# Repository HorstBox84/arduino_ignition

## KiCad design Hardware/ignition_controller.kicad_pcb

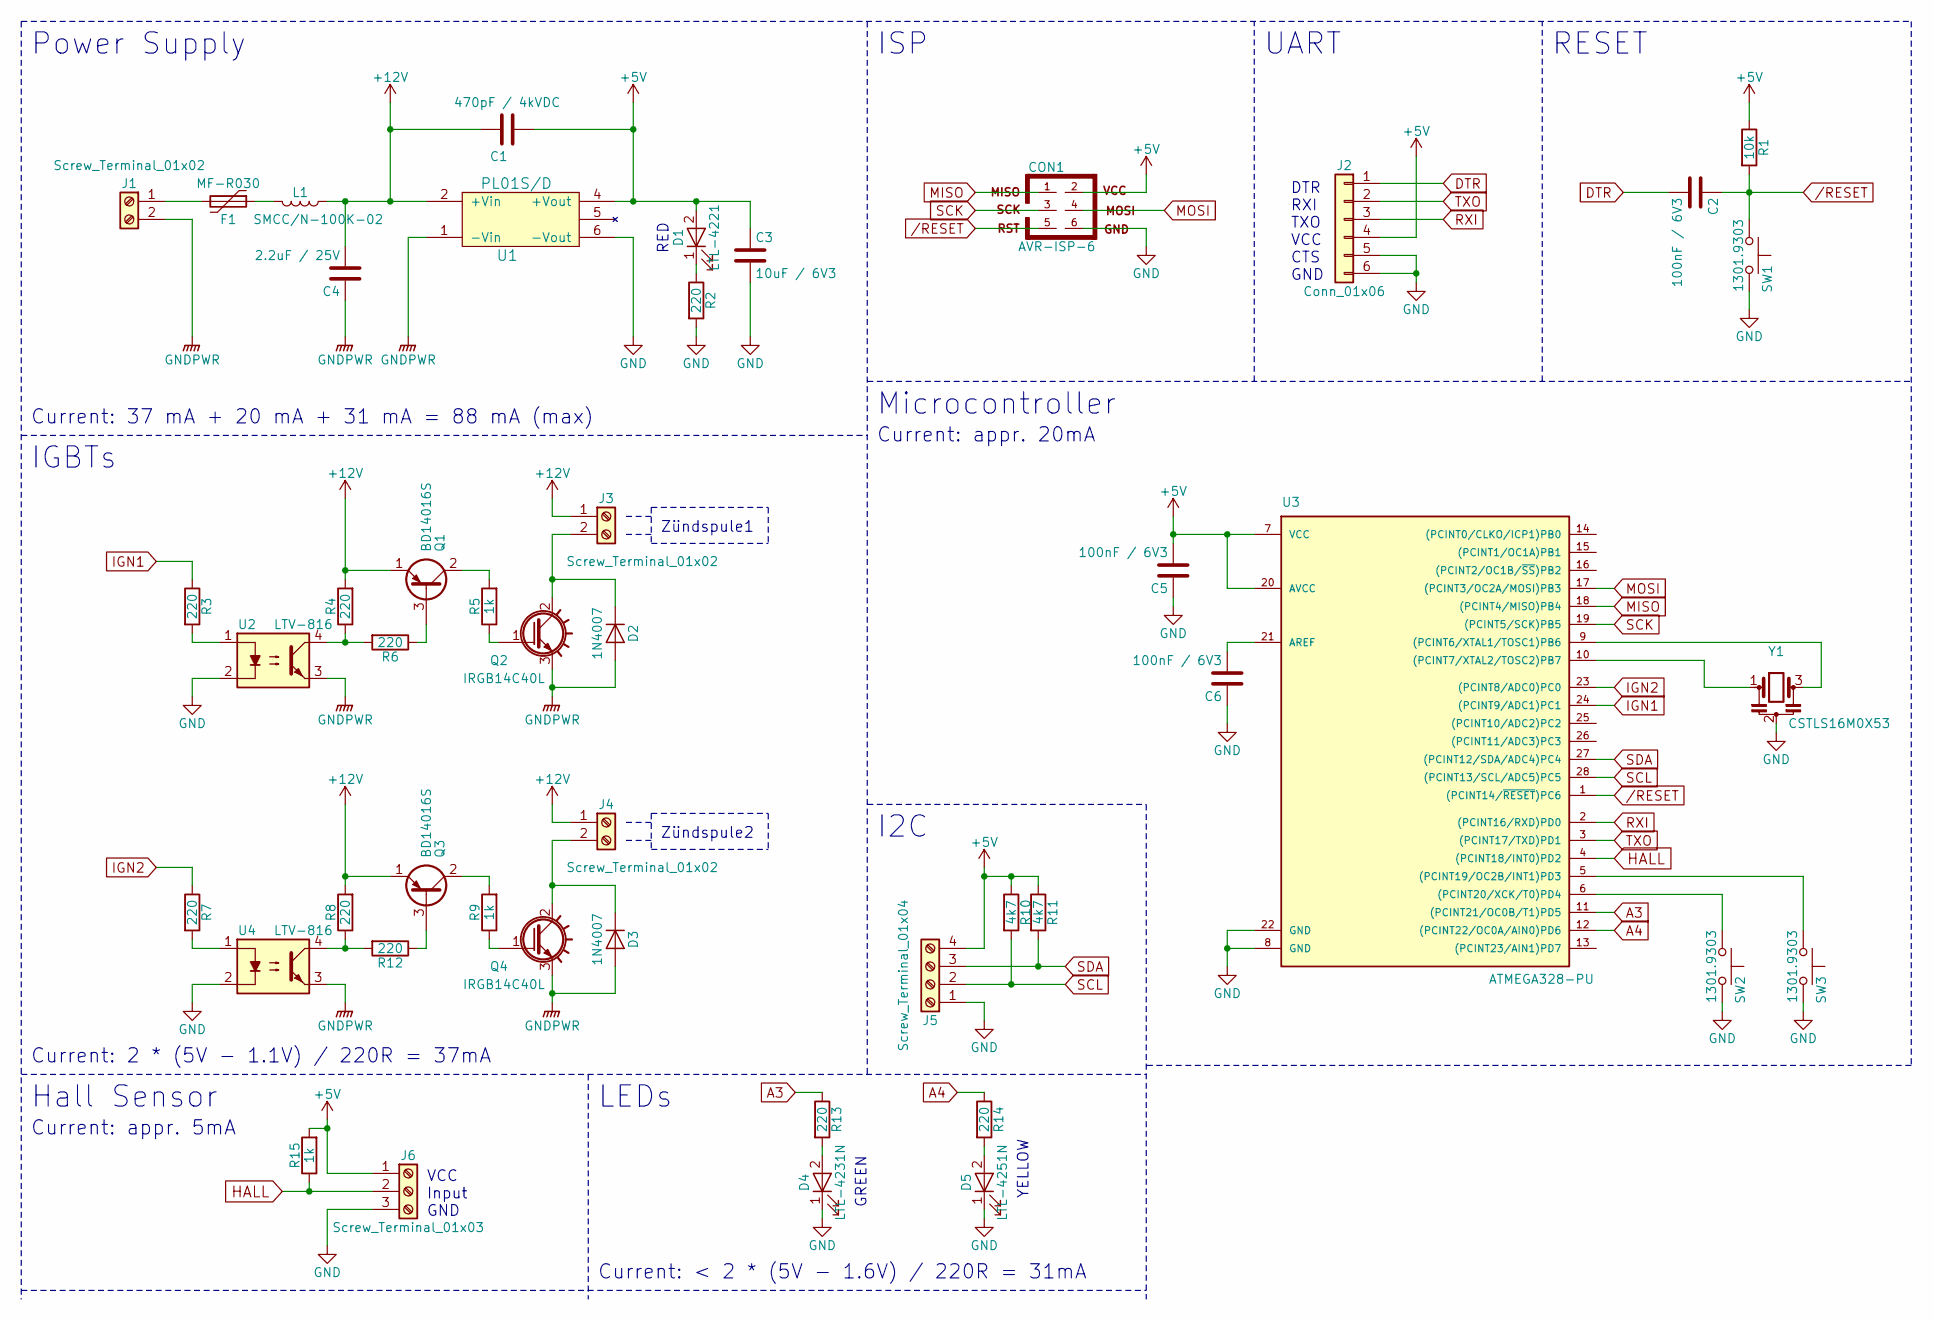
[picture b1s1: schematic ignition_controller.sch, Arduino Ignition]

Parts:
C1: 470pF / 4kVDC; C_Disc_D6_P5
C2, C5, C6: 100nF / 6V3; C_Disc_D3_P2.5
C3: 10uF / 6V3; C_Disc_D6_P5
C4: 2.2uF / 25V; C_Disc_D3_P2.5
CON1: AVR-ISP-6; Pin_Header_Straight_2x03_Pitch2.54mm
D1: LTL-4221; LED-3MM
D2, D3: 1N4007; Diode_DO-41_SOD81_Vertical_KathodeUp
D4: LTL-4231N; LED-3MM
D5: LTL-4251N; LED-3MM
F1: MF-R030; C_Disc_D7.5_P5
J1, J3, J4: Screw_Terminal_01x02; TerminalBlock_Pheonix_PT-3.5mm_2pol
J2: Conn_01x06; Pin_Header_Straight_1x06_Pitch2.54mm
J5: Screw_Terminal_01x04; TerminalBlock_Pheonix_PT-3.5mm_4pol
J6: Screw_Terminal_01x03; TerminalBlock_Pheonix_PT-3.5mm_3pol
L1: SMCC/N-100K-02; Resistor_Vertical_RM5mm
Q1, Q3: BD14016S; TO-126_Vertical
Q2, Q4: IRGB14C40L; TO-220_Neutral123_Vertical
R1: 10k; Resistor_Vertical_RM5mm
R2, R3, R4, R6, R7, R8, R12, R13, R14: 220; Resistor_Vertical_RM5mm
R5, R9, R15: 1k; Resistor_Vertical_RM5mm
R10, R11: 4k7; Resistor_Vertical_RM5mm
SW1, SW2, SW3: 1301.9303; SW_PUSH_6mm_h7.3mm
U1: PL01S/D; DCDC-Conv_TRACO_TMR_1-xxxx_Dual
U2, U4: LTV-816; DIP-4_W7.62mm
U3: ATMEGA328-PU; DIP-28_W7.62mm_LongPads
Y1: CSTLS16M0X53; Resonator-3pin_w6.0mm_h3.0mm

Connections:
+5V: C1.1, C3.1, C5.2, CON1.2, D1.2 (A), J2.4, J5.4, J6.1, R1.1, R10.1, R11.1, R15.2, U1.4 (+Vout), U3.7 (VCC), U3.20 (AVCC)
+12V: C1.2, C4.2, J3.1, J4.1, L1.1, Q1.1 (E), Q3.1 (E), R4.2, R8.2, U1.2 (+Vin)
/RESET: C2.1, CON1.5, R1.2, SW1.1, U3.1 ((PCINT14/~RESET~)PC6)
A3: R13.1, U3.11 ((PCINT21/OC0B/T1)PD5)
A4: R14.1, U3.12 ((PCINT22/OC0A/AIN0)PD6)
DTR: C2.2, J2.1
GND: C3.2, C5.1, C6.1, CON1.6, D4.1 (K), D5.1 (K), J2.5, J2.6, J5.1, J6.3, R2.2, SW1.2, SW2.2, SW3.2, U1.6 (-Vout), U2.2, U3.8 (GND), U3.22 (GND), U4.2, Y1.2
GNDPWR: C4.1, D2.2 (A), D3.2 (A), J1.2, Q2.3 (E), Q4.3 (E), U1.1 (-Vin), U2.3, U4.3
HALL: J6.2, R15.1, U3.4 ((PCINT18/INT0)PD2)
IGN1: R3.1, U3.24 ((PCINT9/ADC1)PC1)
IGN2: R7.1, U3.23 ((PCINT8/ADC0)PC0)
MISO: CON1.1, U3.18 ((PCINT4/MISO)PB4)
MOSI: CON1.4, U3.17 ((PCINT3/OC2A/MOSI)PB3)
unnamed: C6.2, U3.21 (AREF)
unnamed: D1.1 (K), R2.1
unnamed: D2.1 (K), J3.2, Q2.2 (C)
unnamed: D3.1 (K), J4.2, Q4.2 (C)
unnamed: D4.2 (A), R13.2
unnamed: D5.2 (A), R14.2
unnamed: F1.1, L1.2
unnamed: F1.2, J1.1
unnamed: Q1.2 (C), R5.2
unnamed: Q1.3 (B), R6.1
unnamed: Q2.1 (G), R5.1
unnamed: Q3.2 (C), R9.2
unnamed: Q3.3 (B), R12.1
unnamed: Q4.1 (G), R9.1
unnamed: R3.2, U2.1
unnamed: R4.1, R6.2, U2.4
unnamed: R7.2, U4.1
unnamed: R8.1, R12.2, U4.4
unnamed: SW2.1, U3.6 ((PCINT20/XCK/T0)PD4)
unnamed: SW3.1, U3.5 ((PCINT19/OC2B/INT1)PD3)
unnamed: U3.9 ((PCINT6/XTAL1/TOSC1)PB6), Y1.3
unnamed: U3.10 ((PCINT7/XTAL2/TOSC2)PB7), Y1.1
RXI: J2.3, U3.2 ((PCINT16/RXD)PD0)
SCK: CON1.3, U3.19 ((PCINT5/SCK)PB5)
SCL: J5.2, R10.2, U3.28 ((PCINT13/SCL/ADC5)PC5)
SDA: J5.3, R11.2, U3.27 ((PCINT12/SDA/ADC4)PC4)
TXO: J2.2, U3.3 ((PCINT17/TXD)PD1)

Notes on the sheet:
DTR RXI TXO VCC CTS GND
Zündspule1
Microcontroller
ISP
UART
RESET
Power Supply
IGBTs
Hall Sensor
LEDs
VCC Input GND
Zündspule2
Current: appr. 20mA
Current: appr. 5mA
Current: < 2 * (5V - 1.6V) / 220R = 31mA
Current: 2 * (5V - 1.1V) / 220R = 37mA
Current: 37 mA + 20 mA + 31 mA = 88 mA (max)
I2C
RED
GREEN
YELLOW

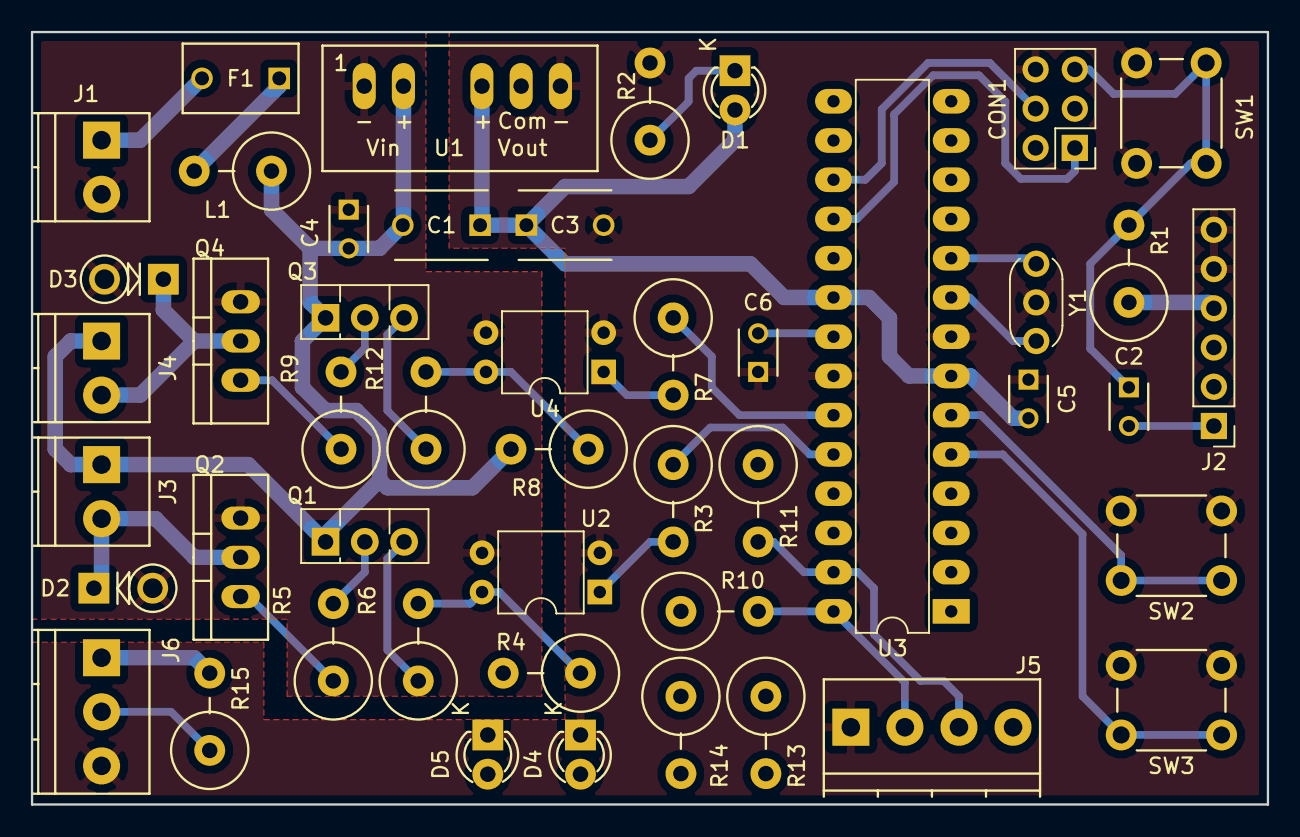
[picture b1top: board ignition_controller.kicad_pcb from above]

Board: 2 copper layers, 80.0 x 50.0 mm, 47 parts (0 on the bottom side), 40 nets.

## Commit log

2017-09-20 :boom::camel: Added .gitattributes & .gitignore files
2017-09-20 added folder structure
